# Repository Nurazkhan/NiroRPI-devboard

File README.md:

# NiroRPI development Board
Customizing RPI2040 devboard and learning! \

---
The NiroRPI board consists of several parts.
First of all it is MCU RPI2040 the brain of the board.
Then you have to gave a memory to the brain, for which QSPI flash memory is responsible for. Another think dev board requires is clock, all crystall oscillator included in the design.
Also, we can't forget about power for which we use USB type C female port.
And we have to decrease it from 5V to 3V3 by linear stabilizator. Apart from that we have to handle noises for which decoupling capacitors where used. Of course you have to add your soul when making project. My piece of soul is in silksreen art.
 
### Unique Feature
- LiPo battery Charging 
The devboard includes capabilities to operate with LiPo Battery. This is achieved by 2 parts.
1. Power Switching Mosfet AO3401A allows to operate devboard on USB C, when connected. And seemlessly switches power supply to batter when USB C removed. This significantly Improves mobility of this devboard.
2. MCP73831 Main Charger IC, which allows to charge the battery while USB C is connected. It also provides information whether battery is currently charging or fully charged on GPIO 25. On GPIO 29 it the voltage divider is set and the percentage of battery can be seen.

## Basic Firmware
Basic firmware is writting in micropython. By default, when connected to device it sends battery connection and percentage charge information over serial.

---
## BOM
| Name | Value | Quantity | Price | Min Buy Price | Link |
|---|---|---|---|---|---|
| 0402 Capacitor | 1uF | 2pc | $0.04/pc |$2.0| [link](https://www.aliexpress.com/item/1005007464553853.html?spm=a2g0o.productlist.main.1.33eb13c3a1sww9&algo_pvid=1ce3280b-b1ce-44b2-9360-706b783c74bf&algo_exp_id=1ce3280b-b1ce-44b2-9360-706b783c74bf-0&pdp_ext_f=%7B%22order%22%3A%227563%22%2C%22eval%22%3A%221%22%2C%22fromPage%22%3A%22search%22%7D&pdp_npi=6%40dis%21EUR%211.90%211.90%21%21%2113.91%2113.91%21%402101d3fe17928380017475844e0d06%2112000040865339092%21sea%21FI%210%21ABX%211%210%21n_tag%3A-29910%3Bd%3A6cea0dff%3Bm03_new_user%3A-29895&curPageLogUid=Z1IctUtDfu5q&utparam-url=scene%3Asearch%7Cquery_from%3A%7Cx_object_id%3A1005007464553853%7C_p_origin_prod%3A) |
| 0402 Capacitor | 0.1uF | 10pc | $0.01/pc |$1.24 | [link](https://www.aliexpress.com/item/1005007464553853.html?spm=a2g0o.productlist.main.1.33eb13c3a1sww9&algo_pvid=1ce3280b-b1ce-44b2-9360-706b783c74bf&algo_exp_id=1ce3280b-b1ce-44b2-9360-706b783c74bf-0&pdp_ext_f=%7B%22order%22%3A%227563%22%2C%22eval%22%3A%221%22%2C%22fromPage%22%3A%22search%22%7D&pdp_npi=6%40dis%21EUR%211.90%211.90%21%21%2113.91%2113.91%21%402101d3fe17928380017475844e0d06%2112000040865339092%21sea%21FI%210%21ABX%211%210%21n_tag%3A-29910%3Bd%3A6cea0dff%3Bm03_new_user%3A-29895&curPageLogUid=Z1IctUtDfu5q&utparam-url=scene%3Asearch%7Cquery_from%3A%7Cx_object_id%3A1005007464553853%7C_p_origin_prod%3A) |
| 0603 Capacitor | 10uF | 2pc |$0.04|$1.9 | [link](https://www.aliexpress.com/item/1005007464553853.html?spm=a2g0o.productlist.main.9.87fc746aci5ff1&algo_pvid=1cc057ad-403e-4677-b3e2-52de9274ed6d&algo_exp_id=1cc057ad-403e-4677-b3e2-52de9274ed6d-8&pdp_ext_f=%7B%22order%22%3A%227563%22%2C%22eval%22%3A%221%22%2C%22fromPage%22%3A%22search%22%7D&pdp_npi=6%40dis%21EUR%211.90%211.90%21%21%2113.91%2113.91%21%402103128817928387387008370e0fea%2112000040865339092%21sea%21FI%210%21ABX%211%210%21n_tag%3A-29910%3Bd%3A6cea0dff%3Bm03_new_user%3A-29895&curPageLogUid=COmJyo83HHxI&utparam-url=scene%3Asearch%7Cquery_from%3A%7Cx_object_id%3A1005007464553853%7C_p_origin_prod%3A) |
| 0402 Capacitor | 33pF | 2pc | $0.0033| $0.66| [link](https://www.aliexpress.com/item/1005004406012464.html?spm=a2g0o.productlist.main.1.23ab6a5cs8UpD1&algo_pvid=e5c2a926-7419-43f5-b501-cb0d19053b9e&algo_exp_id=e5c2a926-7419-43f5-b501-cb0d19053b9e-0&pdp_ext_f=%7B%22order%22%3A%2212%22%2C%22eval%22%3A%221%22%2C%22fromPage%22%3A%22search%22%7D&pdp_npi=6%40dis%21EUR%210.68%210.66%21%21%210.74%210.73%21%402101c28d17928387970034540e0f4e%2112000029066067966%21sea%21FI%210%21ABX%211%210%21n_tag%3A-29910%3Bd%3A6cea0dff%3Bm03_new_user%3A-29895&curPageLogUid=WZNt2OROy7tG&utparam-url=scene%3Asearch%7Cquery_from%3A%7Cx_object_id%3A1005004406012464%7C_p_origin_prod%3A) |
| USB-C Receptacle (14P USB 2.0) | TYPE-C-31-M-12 | 1pc |$0.242 |$2.42 | [link](https://www.aliexpress.com/item/1005005243706874.html?spm=a2g0o.productlist.main.10.12eaHq6sHq6sGj&algo_pvid=13872c83-4cb9-495c-b3a4-1da70454aa21&algo_exp_id=13872c83-4cb9-495c-b3a4-1da70454aa21-9&pdp_ext_f=%7B%22order%22%3A%2231%22%2C%22eval%22%3A%221%22%2C%22fromPage%22%3A%22search%22%7D&pdp_npi=6%40dis%21EUR%212.43%212.42%21%21%212.66%212.65%21%402101d3fe17928388447731083e0ffd%2112000047882262162%21sea%21FI%210%21ABX%211%210%21n_tag%3A-29910%3Bd%3A6cea0dff%3Bm03_new_user%3A-29895&curPageLogUid=PttTDNerzeWs&utparam-url=scene%3Asearch%7Cquery_from%3A%7Cx_object_id%3A1005005243706874%7C_p_origin_prod%3A) |
| 1x20 Pin Header 2.54mm Vertical | 20-Pin | 3pc | $0.13|$1.3| [link](https://www.aliexpress.com/item/32852994833.html?spm=a2g0o.productlist.main.6.404a3506hWddBQ&algo_pvid=d78fc8ff-5bb9-4a57-bbb9-f1c1981b464a&algo_exp_id=d78fc8ff-5bb9-4a57-bbb9-f1c1981b464a-5&pdp_ext_f=%7B%22order%22%3A%2247%22%2C%22eval%22%3A%221%22%2C%22fromPage%22%3A%22search%22%7D&pdp_npi=6%40dis%21EUR%211.29%211.29%21%21%211.41%211.41%21%402103128917928388958431185e0fb8%2165253578747%21sea%21FI%210%21ABX%211%210%21n_tag%3A-29910%3Bd%3A6cea0dff%3Bm03_new_user%3A-29895&curPageLogUid=S8hGZYq8zqir&utparam-url=scene%3Asearch%7Cquery_from%3A%7Cx_object_id%3A32852994833%7C_p_origin_prod%3A) |
| 0402 Resistor | 5.1K | 2pc |$0.0096 | $0.96| [link](https://www.aliexpress.com/item/1005008478030316.html?spm=a2g0o.productlist.main.1.16225234B0zsth&algo_pvid=92a6730b-c8ab-46c1-be69-e29c4405b7e8&algo_exp_id=92a6730b-c8ab-46c1-be69-e29c4405b7e8-0&pdp_ext_f=%7B%22order%22%3A%2273%22%2C%22eval%22%3A%221%22%2C%22fromPage%22%3A%22search%22%7D&pdp_npi=6%40dis%21EUR%210.96%210.96%21%21%217.02%217.02%21%402101c28d17928390013176345e0e88%2112000045322226533%21sea%21FI%210%21ABX%211%210%21n_tag%3A-29910%3Bd%3A6cea0dff%3Bm03_new_user%3A-29895&curPageLogUid=txJdVtTcEzpI&utparam-url=scene%3Asearch%7Cquery_from%3A%7Cx_object_id%3A1005008478030316%7C_p_origin_prod%3A) |
| 0402 Resistor | 27R | 2pc | $0.0096|$0.96| | [link](https://www.aliexpress.com/item/1005008478030316.html?spm=a2g0o.productlist.main.1.16225234B0zsth&algo_pvid=92a6730b-c8ab-46c1-be69-e29c4405b7e8&algo_exp_id=92a6730b-c8ab-46c1-be69-e29c4405b7e8-0&pdp_ext_f=%7B%22order%22%3A%2273%22%2C%22eval%22%3A%221%22%2C%22fromPage%22%3A%22search%22%7D&pdp_npi=6%40dis%21EUR%210.96%210.96%21%21%217.02%217.02%21%402101c28d17928390013176345e0e88%2112000045322226533%21sea%21FI%210%21ABX%211%210%21n_tag%3A-29910%3Bd%3A6cea0dff%3Bm03_new_user%3A-29895&curPageLogUid=txJdVtTcEzpI&utparam-url=scene%3Asearch%7Cquery_from%3A%7Cx_object_id%3A1005008478030316%7C_p_origin_prod%3A) |
| 0402 Resistor | 1K | 2pc |$0.0096 | $0.96|| [link](https://www.aliexpress.com/item/1005008478030316.html?spm=a2g0o.productlist.main.1.16225234B0zsth&algo_pvid=92a6730b-c8ab-46c1-be69-e29c4405b7e8&algo_exp_id=92a6730b-c8ab-46c1-be69-e29c4405b7e8-0&pdp_ext_f=%7B%22order%22%3A%2273%22%2C%22eval%22%3A%221%22%2C%22fromPage%22%3A%22search%22%7D&pdp_npi=6%40dis%21EUR%210.96%210.96%21%21%217.02%217.02%21%402101c28d17928390013176345e0e88%2112000045322226533%21sea%21FI%210%21ABX%211%210%21n_tag%3A-29910%3Bd%3A6cea0dff%3Bm03_new_user%3A-29895&curPageLogUid=txJdVtTcEzpI&utparam-url=scene%3Asearch%7Cquery_from%3A%7Cx_object_id%3A1005008478030316%7C_p_origin_prod%3A) |
| 0402 Resistor | 10K | 1pc | $0.0096| $0.96|| [link](https://www.aliexpress.com/item/1005008478030316.html?spm=a2g0o.productlist.main.1.16225234B0zsth&algo_pvid=92a6730b-c8ab-46c1-be69-e29c4405b7e8&algo_exp_id=92a6730b-c8ab-46c1-be69-e29c4405b7e8-0&pdp_ext_f=%7B%22order%22%3A%2273%22%2C%22eval%22%3A%221%22%2C%22fromPage%22%3A%22search%22%7D&pdp_npi=6%40dis%21EUR%210.96%210.96%21%21%217.02%217.02%21%402101c28d17928390013176345e0e88%2112000045322226533%21sea%21FI%210%21ABX%211%210%21n_tag%3A-29910%3Bd%3A6cea0dff%3Bm03_new_user%3A-29895&curPageLogUid=txJdVtTcEzpI&utparam-url=scene%3Asearch%7Cquery_from%3A%7Cx_object_id%3A1005008478030316%7C_p_origin_prod%3A) |
| Push Button Switch (SPST-NO Alps SKRK) | SW_Push | 1pc |$0.006 |$3 | [link](https://www.aliexpress.com/ssr/300000512/BundleDealsDutyCovered?spm=a2g0o.productlist.main.23.7e7a2c00YkpvcS&businessCode=guide&productIds=1005004297433455:12000028671475705&pha_manifest=ssr&_immersiveMode=true&disableNav=YES&sourceName=SEARCHProduct&utparam-url=scene%3Asearch%7Cquery_from%3A%7Cx_object_id%3A1005004297433455%7C_p_origin_prod%3A&pvid=fc01f38c-ee70-429d-b7e2-153687f90f3d) |
| Microcontroller QFN-56 | RP2040 | 1pc |$2.32|$4.64 | [link](https://www.aliexpress.com/item/1005006481247856.html?spm=a2g0o.productlist.main.4.5a505ec380vjfe&algo_pvid=3f1055b4-faed-4b31-8ca6-28018250ebfc&algo_exp_id=3f1055b4-faed-4b31-8ca6-28018250ebfc-3&pdp_ext_f=%7B%22order%22%3A%2229%22%2C%22eval%22%3A%221%22%2C%22fromPage%22%3A%22search%22%7D&pdp_npi=6%40dis%21EUR%214.64%214.64%21%21%2133.87%2133.87%21%402101c69517928391673802988e0ebd%2112000037358586395%21sea%21FI%210%21ABX%211%210%21n_tag%3A-29910%3Bd%3A6cea0dff%3Bm03_new_user%3A-29895&curPageLogUid=oizp8OHJRp5m&utparam-url=scene%3Asearch%7Cquery_from%3A%7Cx_object_id%3A1005006481247856%7C_p_origin_prod%3A) |
| LDO Voltage Regulator SOT-23 | MCP1700x-330xxTT | 1pc |$0.235 |$2.35| [link](https://www.aliexpress.com/item/1005010457470744.html?spm=a2g0o.productlist.main.2.91dc494alLmY3r&algo_pvid=7206a0b7-3823-4af5-9f48-fe7043e7341e&algo_exp_id=7206a0b7-3823-4af5-9f48-fe7043e7341e-1&pdp_ext_f=%7B%22order%22%3A%222%22%2C%22eval%22%3A%221%22%2C%22fromPage%22%3A%22search%22%7D&pdp_npi=6%40dis%21EUR%212.35%212.35%21%21%212.57%212.57%21%402101de2517928392481461068e10fb%2112000052477027046%21sea%21FI%210%21ABX%211%210%21n_tag%3A-29910%3Bd%3A6cea0dff%3Bm03_new_user%3A-29895&curPageLogUid=GqBMlJZrs2cj&utparam-url=scene%3Asearch%7Cquery_from%3A%7Cx_object_id%3A1005010457470744%7C_p_origin_prod%3A) |
| NOR Flash Memory USON-8 (128Mb) | W25Q128JVS | 1pc |$0.61|$0.61 | [link](https://www.aliexpress.com/item/1005009949894136.html?spm=a2g0o.productlist.main.2.5a14104daznULO&algo_pvid=a36b1a77-d764-4ee7-8480-798defc4a4a6&algo_exp_id=a36b1a77-d764-4ee7-8480-798defc4a4a6-1&pdp_ext_f=%7B%22order%22%3A%22340%22%2C%22eval%22%3A%221%22%2C%22fromPage%22%3A%22search%22%7D&pdp_npi=6%40dis%21EUR%210.62%210.61%21%21%214.52%214.52%21%40210311c217928392961714942e0ff9%2112000050659133711%21sea%21FI%210%21ABX%211%210%21n_tag%3A-29910%3Bd%3A6cea0dff%3Bm03_new_user%3A-29895&curPageLogUid=moexlDes1oED&utparam-url=scene%3Asearch%7Cquery_from%3A%7Cx_object_id%3A1005009949894136%7C_p_origin_prod%3A) |
| Crystal SMD 3225-4Pin | 12MHz | 1pc | $0.3| $2.75| [link](https://www.aliexpress.com/item/1005007282073350.html?spm=a2g0o.productlist.main.1.42a54506vpAb9t&algo_pvid=00cde798-dc2c-4c5d-b74c-cf3e82a695be&algo_exp_id=00cde798-dc2c-4c5d-b74c-cf3e82a695be-0&pdp_ext_f=%7B%22order%22%3A%2210%22%2C%22eval%22%3A%221%22%2C%22fromPage%22%3A%22search%22%7D&pdp_npi=6%40dis%21EUR%212.75%212.75%21%21%213.01%213.01%21%402101d9ef17928393249016774e10b8%2112000040057852652%21sea%21FI%210%21ABX%211%210%21n_tag%3A-29910%3Bd%3A6cea0dff%3Bm03_new_user%3A-29895&curPageLogUid=GtFPoNpVzfLV&utparam-url=scene%3Asearch%7Cquery_from%3A%7Cx_object_id%3A1005007282073350%7C_p_origin_prod%3A) |
|J5|JSTPH 2pin|1pc|$0.5|$2.5|[link](https://www.aliexpress.com/item/4001253349808.html?spm=a2g0o.productlist.main.1.4730752efq3Fm9&algo_pvid=fb11f401-324a-4e82-91e6-cf09d6a6ee1a&algo_exp_id=fb11f401-324a-4e82-91e6-cf09d6a6ee1a-0&pdp_ext_f=%7B%22order%22%3A%22124%22%2C%22eval%22%3A%221%22%2C%22fromPage%22%3A%22search%22%7D&pdp_npi=6%40dis%21EUR%214.52%212.49%21%21%2132.98%2118.14%21%402101ca9517939409376543958e1017%2110000015480202193%21sea%21FI%210%21X%211%210%21n_tag%3A-29919%3Bd%3A6cea0dff%3Bm03_new_user%3A-29895&curPageLogUid=X3tKrtRrFuud&utparam-url=scene%3Asearch%7Cquery_from%3A%7Cx_object_id%3A4001253349808%7C_p_origin_prod%3A)|
|U4|MCP73831T|1pc|$0.35|$1.5||
|Q1|AO3401A|1pc|$0.10|$1||
|D1|1N5819|1pc|$0.08|$0.8||
|Mini Hotplate|65W|1pc|$20|$20|[link](https://www.aliexpress.com/item/1005007016135854.html)|

*total: ~$30 (if handsoldered) and $76 if to use JLCPCB assempbly* \
**pinheader needs 3 pc, cause instead of ordering 3pin pinheader, you can break from 20pin pinheaders. Anyways you need to order 5 at least, so its cheaper not to buy seperate 3pinheader one.

---
## Scheme

* Pins and connections done using global labels. Scheme seperated in 6 parts.
* Left top corner is TYPE C and Low Voltage regulator.
* Center top is Decoupling capacitors.
* Right top corner is Flash Memory connection scheme.
* Bottom left corner is Pinout for pinheaders
* Center is MCU RPI2040 connection
* and center right is Crystall oscillator connection.

---
## PCB layout

#### Front copper Layer and Back Copper Layer
 
( SilkScreen hidden )

## front and back with silkscreen

## 3D view front and back

# Thank you, hack club!

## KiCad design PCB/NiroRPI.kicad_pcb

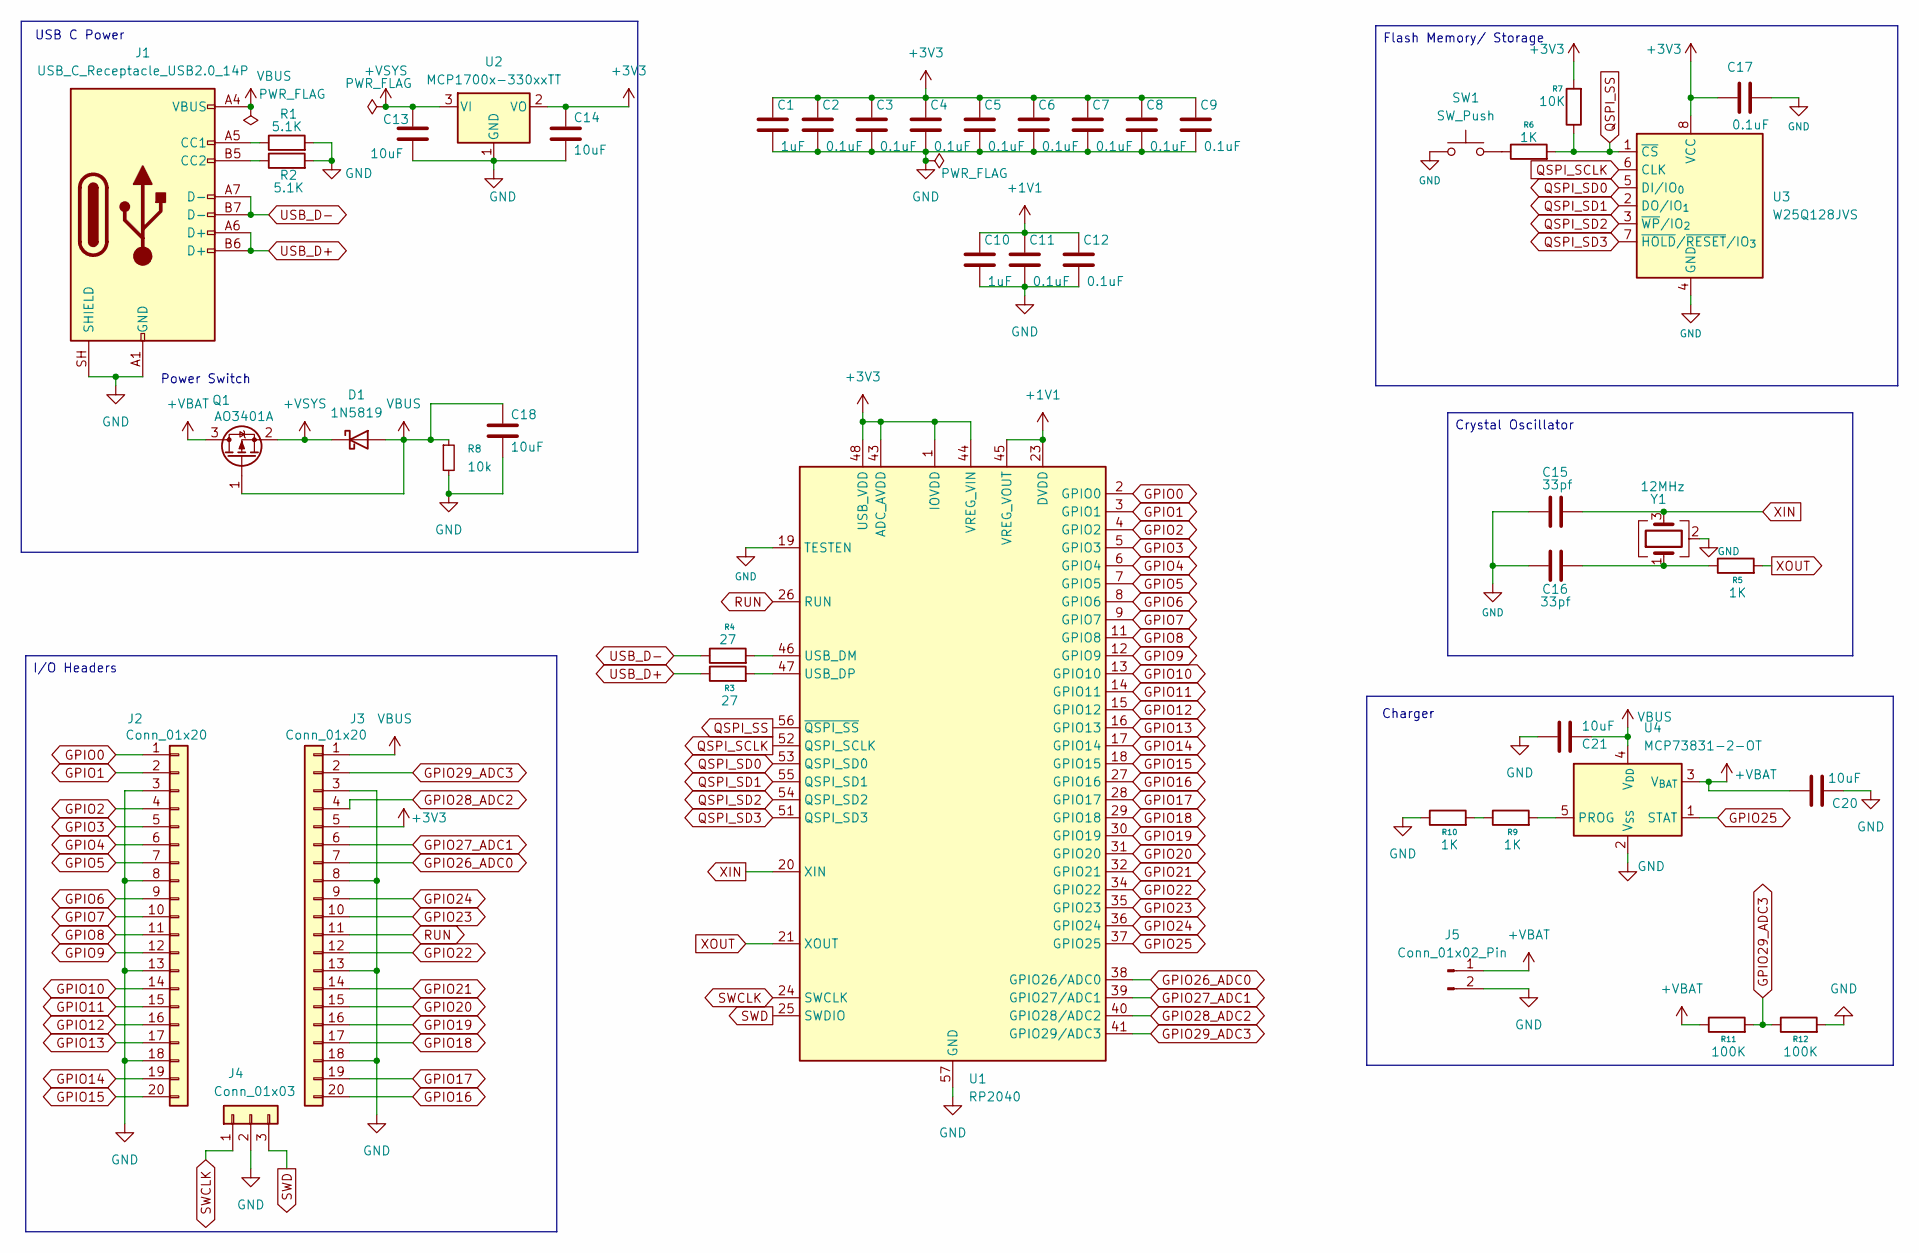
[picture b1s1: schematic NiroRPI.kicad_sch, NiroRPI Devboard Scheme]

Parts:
C1, C10: 1uF; C_0402_1005Metric
C2, C3, C4, C5, C6, C7, C8, C9, C11, C12, C17: 0.1uF; C_0402_1005Metric
C13, C14, C18, C20, C21: 10uF; C_0603_1608Metric
C15, C16: 33pf; C_0402_1005Metric
D1: 1N5819; Nexperia_CFP3_SOD-123W
J1: USB_C_Receptacle_USB2.0_14P; USB_C_Receptacle_HRO_TYPE-C-31-M-12
J2, J3: Conn_01x20; PinHeader_1x20_P2.54mm_Vertical
J4: Conn_01x03; PinHeader_1x03_P2.54mm_Vertical
J5: Conn_01x02_Pin; JST_PH_B2B-PH-K_1x02_P2.00mm_Vertical
Q1: AO3401A; SOT-23
R1, R2: 5.1K; R_0402_1005Metric
R3, R4: 27; R_0402_1005Metric
R5, R6, R9, R10: 1K; R_0402_1005Metric
R7: 10K; R_0402_1005Metric
R8: 10k; R_0402_1005Metric
R11, R12: 100K; R_0402_1005Metric
SW1: SW_Push; SW_Push_SPST_NO_Alps_SKRK
U1: RP2040; QFN-56-1EP_7x7mm_P0.4mm_EP3.2x3.2mm
U2: MCP1700x-330xxTT; SOT-23
U3: W25Q128JVS; Winbond_USON-8-1EP_3x2mm_P0.5mm_EP0.2x1.6mm
U4: MCP73831-2-OT; SOT-23-5
Y1: 12MHz; Crystal_SMD_3225-4Pin_3.2x2.5mm

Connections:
+1V1: C10.1, C11.1, C12.1, U1.23 (DVDD), U1.45 (VREG_VOUT), U1.50 (DVDD)
+3V3: C1.1, C2.1, C3.1, C4.1, C5.1, C6.1, C7.1, C8.1, C9.1, C14.1, C17.1, J3.5, R7.2, U1.1 (IOVDD), U1.10 (IOVDD), U1.22 (IOVDD), U1.33 (IOVDD), U1.42 (IOVDD), U1.43 (ADC_AVDD), U1.44 (VREG_VIN), U1.48 (USB_VDD), U1.49 (IOVDD), U2.2 (VO), U3.8 (VCC)
+VBAT: C20.2, J5.1, Q1.3 (D), R11.1, U4.3 (V_{BAT})
+VSYS: C13.1, D1.1 (K), Q1.2 (S), U2.3 (VI)
GND: C1.2, C2.2, C3.2, C4.2, C5.2, C6.2, C7.2, C8.2, C9.2, C10.2, C11.2, C12.2, C13.2, C14.2, C15.2, C16.2, C17.2, C18.2, C20.1, C21.2, J1.A1 (GND), J1.A12 (GND), J1.B1 (GND), J1.B12 (GND), J1.SH (SHIELD), J2.3, J2.8, J2.13, J2.18, J3.3, J3.8, J3.13, J3.18, J4.2, J5.2, R1.2, R2.2, R8.2, R10.1, R12.2, SW1.1, U1.19 (TESTEN), U1.57 (GND), U2.1 (GND), U3.4 (GND), U4.2 (V_{SS}), Y1.2 (G), Y1.4 (G)
GPIO0: J2.1, U1.2 (GPIO0)
GPIO1: J2.2, U1.3 (GPIO1)
GPIO2: J2.4, U1.4 (GPIO2)
GPIO3: J2.5, U1.5 (GPIO3)
GPIO4: J2.6, U1.6 (GPIO4)
GPIO5: J2.7, U1.7 (GPIO5)
GPIO6: J2.9, U1.8 (GPIO6)
GPIO7: J2.10, U1.9 (GPIO7)
GPIO8: J2.11, U1.11 (GPIO8)
GPIO9: J2.12, U1.12 (GPIO9)
GPIO10: J2.14, U1.13 (GPIO10)
GPIO11: J2.15, U1.14 (GPIO11)
GPIO12: J2.16, U1.15 (GPIO12)
GPIO13: J2.17, U1.16 (GPIO13)
GPIO14: J2.19, U1.17 (GPIO14)
GPIO15: J2.20, U1.18 (GPIO15)
GPIO16: J3.20, U1.27 (GPIO16)
GPIO17: J3.19, U1.28 (GPIO17)
GPIO18: J3.17, U1.29 (GPIO18)
GPIO19: J3.16, U1.30 (GPIO19)
GPIO20: J3.15, U1.31 (GPIO20)
GPIO21: J3.14, U1.32 (GPIO21)
GPIO22: J3.12, U1.34 (GPIO22)
GPIO23: J3.10, U1.35 (GPIO23)
GPIO24: J3.9, U1.36 (GPIO24)
GPIO25: U1.37 (GPIO25), U4.1 (STAT)
GPIO26_ADC0: J3.7, U1.38 (GPIO26/ADC0)
GPIO27_ADC1: J3.6, U1.39 (GPIO27/ADC1)
GPIO28_ADC2: J3.4, U1.40 (GPIO28/ADC2)
GPIO29_ADC3: J3.2, R11.2, R12.1, U1.41 (GPIO29/ADC3)
unnamed: C16.1, R5.1, Y1.1
unnamed: J1.A5 (CC1), R1.1
unnamed: J1.B5 (CC2), R2.1
unnamed: R6.1, SW1.2
unnamed: R9.1, R10.2
unnamed: R4.2, U1.46 (USB_DM)
unnamed: R3.2, U1.47 (USB_DP)
unnamed: R9.2, U4.5 (PROG)
QSPI_SCLK: U1.52 (QSPI_SCLK), U3.6 (CLK)
QSPI_SD0: U1.53 (QSPI_SD0), U3.5 (DI/IO_{0})
QSPI_SD1: U1.55 (QSPI_SD1), U3.2 (DO/IO_{1})
QSPI_SD2: U1.54 (QSPI_SD2), U3.3 (~WP/IO_{2})
QSPI_SD3: U1.51 (QSPI_SD3), U3.7 (~HOLD/~RESET/IO_{3})
QSPI_SS: R6.2, R7.1, U1.56 (~QSPI_SS), U3.1 (~CS)
RUN: J3.11, U1.26 (RUN)
SWCLK: J4.1, U1.24 (SWCLK)
SWD: J4.3, U1.25 (SWDIO)
USB_D+: J1.A6 (D+), J1.B6 (D+), R3.1
USB_D-: J1.A7 (D-), J1.B7 (D-), R4.1
VBUS: C18.1, C21.1, D1.2 (A), J1.A4 (VBUS), J1.A9 (VBUS), J1.B4 (VBUS), J1.B9 (VBUS), J3.1, Q1.1 (G), R8.1, U4.4 (V_{DD})
XIN: C15.1, U1.20 (XIN), Y1.3
XOUT: R5.2, U1.21 (XOUT)

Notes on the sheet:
Power Switch
USB C Power
Charger
I/O Headers
Flash Memory/ Storage
Crystal Oscillator

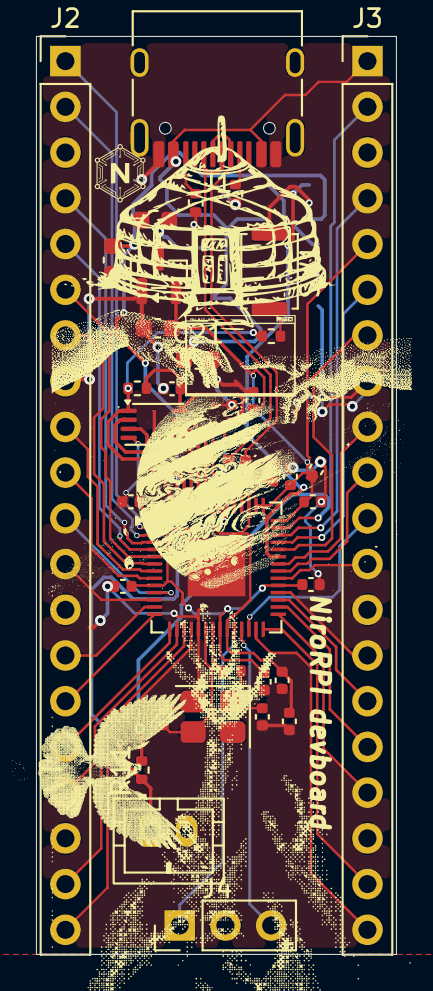
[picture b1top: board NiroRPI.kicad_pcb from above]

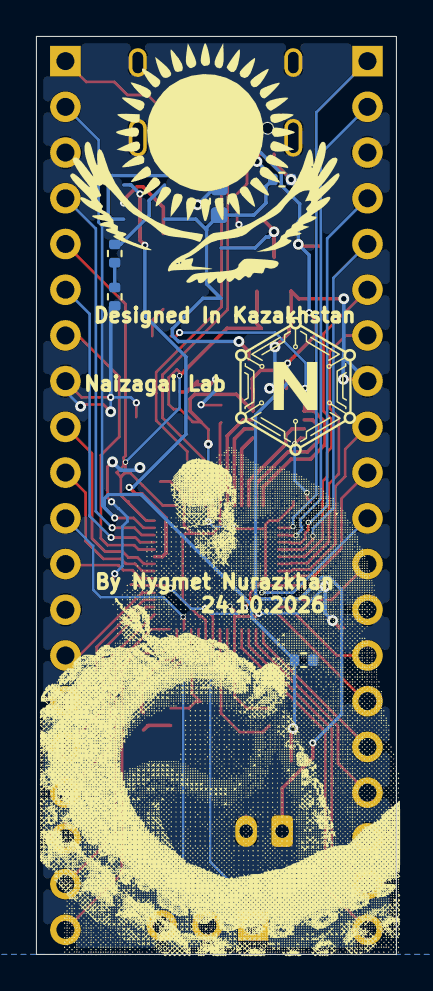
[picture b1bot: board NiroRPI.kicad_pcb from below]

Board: 2 copper layers, 20.0 x 51.0 mm, 42 parts (5 on the bottom side), 55 nets.

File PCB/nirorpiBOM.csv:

Id,Designator,Footprint,Quantity,Comment,Supplier and ref
1,"C1, C10",C_0402_1005Metric,2,1uF,
2,"C2, C3, C4, C5, C6, C7, C8, C9, C11, C17",C_0402_1005Metric,10,0.1uF,
3,"C13, C14",C_0603_1608Metric,2,10uF,
4,"C15, C16",C_0402_1005Metric,2,33pf,
5,J1,USB_C_Receptacle_HRO_TYPE-C-31-M-12,1,USB_C_Receptacle_USB2.0_14P,
6,"J2, J3",PinHeader_1x20_P2.54mm_Vertical,2,Conn_01x20,
7,J4,PinHeader_1x03_P2.54mm_Vertical,1,Conn_01x03,
8,"R1, R2",R_0402_1005Metric,2,5.1K,
9,"R3, R4",R_0402_1005Metric,2,27,
10,"R5, R6",R_0402_1005Metric,2,1K,
11,R7,R_0402_1005Metric,1,10K,
12,SW1,SW_Push_SPST_NO_Alps_SKRK,1,SW_Push,
13,U1,QFN-56-1EP_7x7mm_P0.4mm_EP3.2x3.2mm,1,RP2040,
14,U2,SOT-23,1,MCP1700x-330xxTT,
15,U3,Winbond_USON-8-1EP_3x2mm_P0.5mm_EP0.2x1.6mm,1,W25Q128JVS,
16,Y1,Crystal_SMD_3225-4Pin_3.2x2.5mm,1,12MHz,
